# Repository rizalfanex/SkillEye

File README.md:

# SkillEye: Skeleton-Based Motion Quality Analysis for Racket Sports

Submission for the 8th CTCI Science and Technology Creativity Competition 2026 (Sports theme).

## Abstract

Existing racket-sport analytics apps (e.g. SwingVision) center on ball tracking and match
outcome — where the ball landed, who won the point. SkillEye instead analyzes the player's
*movement*, extracting a normalized 2D skeleton from swing video with RTMPose and modeling it
with a Spatio-Temporal Graph Convolutional Network (ST-GCN), toward the goal of a per-swing
motion-quality score with joint/phase-level error detection and rule-based correction feedback.
This addresses both the "training methods" and "injury prevention" sub-themes of the
competition through one shared representation.

This document reports the technical work completed to date on the [THETIS](https://github.com/THETIS-dataset/dataset)
tennis dataset: a validated pose-extraction pipeline (1,980/1,980 clips, 0 failures), a 6-class
stroke-type classifier (**81.7% ± 4.9%**, 5-fold subject-disjoint cross-validation), and a
beginner-vs-expert motion-quality proxy classifier (**82.4% ± 3.8%**). Both are real trained
results on held-out subjects, not projected targets. A rule-based v1 of that quality-score
system — phase detection, per-joint deviation from expert-clip templates, and generated
correction suggestions — is implemented and demonstrated through an accompanying Streamlit UI.
Section 4 discusses what these results do and do not establish, and Section 5 lays out the
remaining work toward the full quality-score system.

## 1. Introduction

### 1.1 Motivation

Amateur and intermediate racket-sport players typically improve technique through in-person
coaching, which is expensive, geographically limited, and infrequent relative to how often
players practice alone. Video-based swing analysis could close this gap, but existing consumer
tools (SwingVision and similar) are built around ball-tracking and scorekeeping — they answer
"did the shot land in" rather than "what did the player's body do." Movement quality is the
input a coach actually reasons about (elbow position at contact, hip rotation timing, follow-through),
and it is not derivable from ball trajectory alone.

### 1.2 Related Work

The technical approach follows two established lines of work rather than proposing new
architectures: **RTMPose** for real-time 2D human pose estimation, and **ST-GCN**
(Yan, Xiong & Lin, 2018) for skeleton-based action recognition, which models a keypoint sequence
as a spatio-temporal graph — spatial edges follow the human skeleton, temporal edges connect the
same joint across frames. The novelty in SkillEye is the application: using this representation
not just to classify *what* stroke was performed (a mature task), but as the foundation for
scoring *how well* it was performed, which is comparatively unexplored for racket sports at
consumer scale. The THETIS dataset itself (Gourgari et al., CVPR 2013 workshop) was built for
action recognition, not quality assessment — Section 2.1 and 4.1 discuss what that means for
how it can and cannot be used here.

A useful point of comparison is Wagner's tennis serve dataset (2024, [jasnwag/tennis_serve_dataset](https://github.com/jasnwag/tennis_serve_dataset)),
which takes a near-opposite set of trade-offs to THETIS: broadcast footage of the 2024 US Open,
109 professional players, 5,966 serves, with **3D** pose (RTMPose → MotionBERT lifting →
DTW-aligned) rather than 2D, and — notably — an actual serve-quality classification task
(84.0% reported), where THETIS offers only the subject-level beginner/expert proxy used in
Section 2.4/3.2. Table 2 summarizes the contrast:

**Table 2.** Dataset comparison.

| | THETIS (this work) | Wagner tennis serve dataset |
|---|---|---|
| Source | controlled gym recording (Kinect) | broadcast video, 2024 US Open |
| Camera angle | near-frontal | broadcast (side/elevated) |
| Pose dimensionality | 2D (COCO-17) | 3D (COCO-17, MotionBERT-lifted) |
| Subjects | 55 (31 beginner, 24 expert) | 109 professional players |
| Stroke coverage | 12 categories, all strokes | serves only |
| Clips | 1,980 | 5,966 serves |
| Quality ground truth | none (subject-level skill label only) | serve-quality labels available |
| License | dataset's own terms | CC BY 4.0 |

The two datasets are complementary rather than substitutable for this project: THETIS's frontal
angle and 2D pose match what a consumer phone camera can realistically capture (the deployment
target), while the serve dataset's 3D pose and side/elevated broadcast angle are closer to what
the biomechanical joint-angle rules in Section 4.7 of the proposal actually need, and its
existing quality labels are exactly the kind of ground truth Path A/B (Section 5) is trying to
establish independently. It is treated here as a comparative reference and a candidate source
for cross-dataset validation once the 2D pipeline has a 3D-compatible variant, not (yet) as
training or evaluation data for the models in Section 3 — see Section 5 for that as a concrete
next step.

### 1.3 Contributions

1. A validated, resumable pose-extraction pipeline from raw racket-sport video to normalized,
   tracked, single-subject skeleton sequences (Section 2.2).
2. A stroke-type classifier trained from scratch on the extracted skeletons, evaluated with
   5-fold subject-disjoint cross-validation rather than a single split (Section 3.1).
3. Evidence, from a dedicated experiment, that motion *quality* (not just stroke type) is
   learnable from this same skeleton representation — using THETIS's beginner/expert metadata
   as a weak proxy label ahead of real coach-rating ground truth (Section 3.2).
4. An honest accounting of what this dataset cannot yet support (Section 4.1) and a concrete
   plan for closing that gap (Section 5).

## 2. Methodology

### 2.1 Dataset

[THETIS](https://github.com/THETIS-dataset/dataset) (Gourgari et al., 2013) provides 1,980 RGB
video clips across 12 tennis action categories, performed by 55 subjects (**p1–p31 labeled
beginner, p32–p55 labeled expert** per the dataset's own metadata), recorded at ~17–19 fps,
640×480, with a Kinect camera facing the subject (near-frontal, not side-on). Only the
`VIDEO_RGB` subset is used — `VIDEO_Skelet2D/3D` uses Kinect's joint definition (not COCO-17,
the format the deployed pipeline actually produces) and covers only 1,217 of 8,374 sequences,
so it would not be representative even if remapped.

Class composition after the merge described in 2.3 (Table 1):

| stroke | THETIS sub-categories merged | clips |
|---|---|---:|
| backhand | backhand, backhand2hands, backhand_slice | 495 |
| forehand | forehand_flat, forehand_openstands, forehand_slice | 495 |
| backhand_volley | backhand_volley | 165 |
| forehand_volley | forehand_volley | 165 |
| serve | flat_service, kick_service, slice_service | 495 |
| smash | smash | 165 |
| **total** | | **1,980** |

By skill label: 1,116 clips from 31 beginner subjects, 864 clips from 24 expert subjects.

**Measured limitations relevant to this project** (checked directly on sample frames, not
assumed from the dataset paper): the ~17-19fps frame rate is below what the proposal's
biomechanical rules assume is needed to resolve fast strokes (e.g. serves), and the
near-frontal camera angle does not capture the side-on view that joint-angle-based
error-detection rules require. THETIS is therefore treated here as suitable for pretraining the
motion representation and for stroke/skill classification (both established, well-precedented
tasks — this is what Sections 2.3–2.4 and 3 use it for), but **not** as a substitute for
purpose-collected side-view footage when the actual per-swing quality-score model is built
(Section 5).

### 2.2 Pose Extraction Pipeline

Each clip is processed frame-by-frame with **RTMPose** (`rtmpose-s_simcc-body7`, lightweight
mode, COCO-17 keypoints) for pose estimation and **YOLOX-tiny** for person detection, both run
via `rtmlib`/ONNX Runtime. Frames may contain more than one person (other players/staff visible
in the gym), so a dedicated tracking step selects a single, temporally consistent subject:

1. **Primary-subject selection** — on the first frame, the person with the largest visible
   bounding box (among detections with ≥3 confidently-visible joints) is chosen as the subject.
   On subsequent frames, the detection with the nearest hip-center to the previous frame's
   selection is kept, which prevents identity swaps between the subject and any other person
   entering the frame (largest-bbox alone is insufficient once multiple people are present).
2. **Confidence-based interpolation** — per joint, frames below a 0.3 confidence threshold are
   linearly interpolated from the nearest confident frames on either side (no extrapolation at
   clip boundaries). Clips where the primary subject is confidently visible in under 50% of
   frames are dropped rather than interpolated across too large a gap.
3. **Normalization** — each frame is re-centered on the hip midpoint and scaled by
   shoulder-to-hip (torso) length, so the model learns the *shape* of the motion rather than the
   subject's distance from or position relative to the camera.

Result: **1,980/1,980 clips extracted successfully, 0 dropped, 0 failed**, ~1.4s/clip. Code:
`ml/skilleye/skeleton_pipeline.py` (steps above), `ml/skilleye/batch_extract.py` (CLI batch runner,
resumable — skips clips that already have output on disk, so an interrupted run can restart
without redoing completed work).

### 2.3 Stroke Classification Model

THETIS's 12 action categories are merged into 6 target classes (Table 1) reflecting the strokes
the proposal is actually built around — `serve` merges the three service sub-types (genuinely
one stroke with different spin), but `forehand_volley` and `backhand_volley` are kept **separate**
rather than merged into a single "volley" class, since they are visually and kinematically
distinct motions (an earlier iteration that merged them made that class disproportionately hard
to classify — see Section 4.1).

**Architecture**: a compact ST-GCN — 6 spatio-temporal blocks operating on the COCO-17 skeleton
graph (symmetric-normalized adjacency, self-loops included), channel widths 32→64→128→256,
global average pooling, linear classification head. Input is a 4-channel tensor per joint per
frame: 2D position plus its temporal finite-difference (velocity), giving the model direct
access to motion speed/direction rather than only inferring it across pooled layers. Each clip
is time-resampled to a fixed 64 frames (linear interpolation) so variable clip lengths (THETIS
clips range from roughly 2 to 8+ seconds) can be batched. Code: `ml/skilleye/stgcn_model.py`.

**Training**: Adam (lr 1e-3, weight decay 1e-4), cosine-annealed learning rate, class-weighted
cross-entropy (classes are imbalanced — see Table 1), 80–100 epochs, batch size 32. With only 55
subjects total, label-preserving data augmentation is applied at train time: left-right mirroring
(negate the x-coordinate and swap left/right joint indices — a mirrored forehand is still a
forehand, just as a left-handed player's would look), random temporal cropping (retain a random
85–100%-length contiguous sub-window before resampling), and small Gaussian coordinate jitter
(σ=0.02, in normalized units). Code: `ml/skilleye/train_stroke_classifier.py`.

### 2.4 Beginner-vs-Expert Motion-Quality Proxy Model

To test whether motion *quality* — not just stroke identity — is learnable from this
representation, a second model is trained on THETIS's beginner/expert subject-level label
(Section 2.1) as a weak proxy for swing quality, ahead of collecting real coach ratings
(Section 5). Two approaches were tried, reported both for transparency:

- **v1 — hand-crafted features + logistic regression** (`ml/skilleye/beginner_expert_check.py`):
  9 interpretable per-clip features (mean/std swing speed, jerk, elbow/knee joint-angle
  variance, wrist extension range) fed into a linear classifier.
- **v2 — ST-GCN** (`ml/skilleye/train_beginner_expert_stgcn.py`): identical architecture and
  augmentation to Section 2.3, but with a binary beginner/expert output head, trained directly
  on the raw skeleton sequence rather than hand-summarized statistics.

### 2.5 Evaluation Protocol

All splits are **subject-disjoint**: no subject's clips appear in both the training and
validation sets. THETIS clips from the same subject are highly correlated (same body, same
camera, same session), so a clip-level random split would leak subject identity into validation
and overstate accuracy — the model would partly be recognizing *people*, not strokes or skill.

Headline numbers use **5-fold subject-disjoint cross-validation** (`ml/skilleye/cross_validate.py`):
subjects are split into 5 folds, stratified so each fold's held-out group keeps a
beginner/expert mix; each fold trains a fresh model on the other 4 folds' subjects (~44) and
evaluates on the held-out fold's subjects (~11). This is reported as **mean ± standard
deviation across folds**, rather than a single split's number, because with only 55 subjects a
single split's held-out accuracy depends materially on *which* subjects happened to be held
out — the fold-to-fold spread reported in Section 3 is itself informative about that variance.

### 2.6 Quality Scoring System

The proposal's central promised feature -- a per-swing motion-quality score with
per-joint/phase error detection and rule-based correction suggestions (Section 4.7) -- is
implemented here as a rule-based comparison against expert-clip statistics, not a learned
regression model. No coach-rating ground truth exists yet (Path A/B, Section 5), so a
supervised quality-score model cannot be trained honestly; this is an explicitly-scoped
interim v1, in the same spirit as the v1->v2->v3 iterations already described for the
classifiers above.

**Phase detection** (`ml/skilleye/quality/phases.py`): each clip's dominant wrist (whichever
moves more overall -- a proxy for the hitting arm, since THETIS doesn't label handedness)
is used to find the contact frame (peak wrist speed, a standard swing-analysis heuristic),
splitting the clip into three phases: backswing, a short window around contact, and
follow-through.

**Joint angles** (`ml/skilleye/quality/angles.py`): per phase, four flexion angles
(left/right elbow, left/right knee) plus a trunk-rotation proxy (shoulder-line vs.
hip-line angle) are averaged into one scalar per (phase, joint).

**Expert templates** (`ml/skilleye/build_expert_templates.py`, run once offline): for each
stroke class, the mean and standard deviation of each (phase, joint) scalar across that
class's expert-labeled clips, computed only from the training side of this project's
standard subject-disjoint split (Section 2.5) -- never from the held-out validation
subjects, which remain available as genuinely unseen demo inputs.

**Scoring** (`ml/skilleye/quality/score.py`): a query clip's (phase, joint) scalars are
z-scored against its predicted stroke's template; |z| > 1.5 is flagged and mapped to a
fixed coaching-tip sentence, and the overall 0-100 score is a monotonic function of mean
absolute deviation. `SCORE_SCALE`/`FLAG_THRESHOLD` are sanity-checked (Section 3.3), not
formally calibrated -- that calibration is exactly what Path A/B ground truth would
enable.

**Demo UI** (`ml/skilleye/app.py`, Streamlit): pick a stroke category and a sample clip
(restricted to the held-out validation subjects, so every demo score is computed against
a template that never saw that subject) and see the skeleton, the existing stroke
classifier's prediction, the quality score, the per-phase/joint table, and the correction
suggestions together. Run with `streamlit run app.py` from `ml/skilleye/`.

**AI-generated explanation (optional)**: a "Generate AI explanation" button in the demo
UI rewrites the already-flagged deviations above into one natural coaching paragraph via
an LLM (NVIDIA's build.nvidia.com API). The LLM is only ever given the (phase, joint,
z-score) rows the rule-based system already flagged — it never inspects raw angles or
introduces a new diagnosis — so this is a communication layer over the existing,
smoke-checked scoring system, not a new source of truth. It requires an `NVIDIA_API_KEY`
environment variable; without one (or if the API call fails for any reason), the button
falls back to a short warning and the rule-based suggestions list above remains the
result, so the demo never depends on network access to function. Design:
`docs/superpowers/specs/2026-07-23-llm-correction-explainer-design.md`.

### 2.7 Sensor-Fusion Extension (Prototype)

A team discussion identified a concrete limitation already described in Section 4.1: a
single frontal 2D camera cannot see racket-face angle or wrist-snap dynamics at contact —
exactly the kind of high-frequency, off-camera-plane signal a racket-mounted IMU
(accelerometer + gyroscope) would capture directly. This section covers both halves of
that work: the hardware (designed by a teammate, in parallel with everything else in this
document) and the software fusion prototype that will eventually consume its data.

**Hardware — rev1.0 schematics** (designed by [@kyriosaa](https://github.com/kyriosaa)):
an ESP32-C6-WROOM-1 microcontroller paired with an ST LSM6DSO 6-axis IMU
(accelerometer + gyroscope) for sensing, a TP4056/DW01A/FS8205A single-cell Li-ion
charging and protection circuit, and an HT7833 regulator for the board's 3.3V rail.
Full KiCad project: `hardware/skilleye_prototype/` (schematics, PCB layout, component
libraries, datasheets); rendered schematic sheets below, source at
`docs/schematics/prototype/rev1.0/`.

| Charging | MCU + IMU | Regulator |
|---|---|---|
|  |  |  |

This is schematic-complete design work, not yet a built board: no physical prototype has
been assembled, no firmware has been written, and no real sensor data has been collected.
The modeling work below is written accordingly — it does not depend on or wait for the
physical board, and does not claim to have used it.

**Software architecture** (`ml/skilleye/imu_fusion.py`): `STGCN` is refactored to expose
its pooled pre-classifier features via `extract_features()` (`ml/skilleye/stgcn_model.py`,
backward compatible — every existing caller is unaffected). A small `IMUEncoder` (1D-CNN
over a 6-channel accelerometer+gyroscope stream) is fused with that skeleton branch via
concatenation before one classification head (`FusedBeginnerExpertModel`), targeting the
beginner/expert distinction specifically, since that is the axis this sensor is meant to
inform.

**Synthetic data, stated plainly**: because no real sensor data exists yet,
`synthetic_imu_from_skeleton()` derives a placeholder signal from the skeleton itself
(wrist acceleration, forearm angular velocity) rather than from a real sensor. This signal
is, by construction, redundant with information the skeleton branch already has access to
— so `train_beginner_expert_fusion_prototype.py`'s output is a demonstration that the
fusion architecture and training loop work end to end, **not an accuracy result**, and its
numbers must not be cited alongside Section 3.2's cross-validated 82.4% ± 3.8%.

**Path to real data**: a documented collection protocol (~100-200 Hz logging, a tap-based
manual sync event between the video and IMU streams, resampled to the same fixed frame
count skeletons already use) is in
`docs/superpowers/specs/2026-07-23-imu-fusion-prototype-design.md` — written before the
rev1.0 schematic existed, so it describes a generic MPU6050+ESP32 pairing rather than the
LSM6DSO+ESP32-C6 above; the collection method (sampling rate, sync approach) still applies
unchanged. Swapping `synthetic_imu_from_skeleton()`'s call site for a real-data loader is
the only code change needed once the board above is built and recordings exist.

## 3. Results

### 3.1 Stroke Classification

**81.7% ± 4.9%** held-out accuracy (6-way; majority-class baseline 16.7%), fold range
72.5%–86.1%.

| class | precision | recall | f1 | support |
|---|---:|---:|---:|---:|
| backhand | 0.79 | 0.90 | 0.84 | 495 |
| forehand | 0.87 | 0.79 | 0.83 | 495 |
| backhand_volley | 0.66 | 0.63 | 0.64 | 165 |
| forehand_volley | 0.68 | 0.67 | 0.68 | 165 |
| serve | 0.93 | 0.88 | 0.90 | 495 |
| smash | 0.73 | 0.78 | 0.75 | 165 |

`serve` is the strongest class — mechanically the most distinct motion (toss + overhead
strike). The volley classes are weakest, and the confusion matrix shows *why*: forehand_volley
is confused primarily with forehand, backhand_volley primarily with backhand — i.e. a volley
shares arm-swing kinematics with its groundstroke counterpart, and the near-frontal 2D camera
does not capture the footwork/court-position difference (volleys are played closer to the net)
that would otherwise disambiguate them. This is discussed further in Section 4.1.

### 3.2 Beginner vs. Expert

**82.4% ± 3.8%** held-out accuracy (2-way; majority-class baseline 54.6%), fold range
78.5%–89.7%. The v1→v2 progression:

| iteration | method | held-out accuracy |
|---|---|---|
| v1 | 9 hand-crafted features + logistic regression, single split | 58.6% (baseline 54.6%) |
| v2 | ST-GCN on raw skeleton sequence, single split | 76.0% |
| **v3** | **ST-GCN, 5-fold cross-validation** | **82.4% ± 3.8%** |

v1 established that *population-level* differences between beginner and expert clips are real
and highly significant (Welch's t-test on all 9 features, p<0.02, most p<1e-10, n=1,980) —
notably, **experts showed higher swing speed, jerk, and joint-angle variance than beginners, not
lower**, i.e. expert swings read as more dynamic/forceful rather than smoother in this dataset,
which should inform how a smoothness-based quality heuristic is weighted. But v1's linear model
on those 9 summary statistics only reached 58.6% held-out accuracy — barely above baseline,
meaning the signal existed in aggregate but wasn't usable per-subject with simple features.

v2 replaced the hand-crafted features with the same ST-GCN architecture used for stroke
classification, trained directly on the raw skeleton sequence, and reached 76.0% on a single
split. v3 cross-validated that result and found it was, if anything, an *unfavorable* split —
the cross-validated mean (82.4%) is higher than the single-split number, with folds ranging
78.5%–89.7% (Table above; per-class breakdown: beginner precision 0.85/recall 0.83, expert
precision 0.79/recall 0.82, summed over all 5 folds' held-out predictions).

### 3.3 Quality Scoring Smoke Check

No formal ground truth exists yet to validate quality scores against (Section 2.6) --
this instead checks the one directional claim the system must satisfy to be credible:
held-out expert clips should score higher on average than held-out beginner clips, per
stroke class, against that stroke's own expert template.

| stroke | expert mean | beginner mean | experts higher? |
|---|---:|---:|---|
| backhand | 89.8 | 86.2 | yes |
| backhand_volley | 90.9 | 84.6 | yes |
| forehand | 90.1 | 86.6 | yes |
| forehand_volley | 88.9 | 77.5 | yes |
| serve | 87.6 | 87.0 | yes |
| smash | 87.9 | 87.1 | yes |

Experts scored higher on every stroke with held-out data (`ml/skilleye/smoke_check_quality_scoring.py`).
This is a sanity check, not a validation -- it confirms the scoring system's direction
is sane on the same subject-level proxy label used in Section 3.2, not that its absolute
scores or flagged joints are correct at the level of a real coach's judgment. That
remains gated on Path A/B ground truth (Section 5).

The aggregate numbers above are a directional average -- the actual per-clip output looks
like this (two real held-out `forehand_volley` clips, the largest expert/beginner gap in
the table above):

The beginner clip's flagged joints are concrete and actionable (left elbow over-extended,
right elbow under-extended, left knee not bent enough at contact) rather than an opaque
number -- this is what "rule-based correction suggestions" (proposal Section 4.7) actually
produces today, not a mockup of what it might eventually say.

## 4. Discussion

### 4.1 Limitations

- **Camera geometry limits stroke disambiguation.** The volley/groundstroke confusion in
  Section 3.1 is a direct consequence of THETIS's near-frontal camera — footwork and
  court-position cues that would resolve it are not visible from that angle. Side-view footage
  (planned, Section 5) should address this directly, not just improve accuracy but make the
  representation richer for the eventual per-phase error detection this project needs.
- **The beginner/expert label is a subject-level proxy, not a per-swing quality score.** THETIS
  labels an entire subject as beginner or expert; it says nothing about whether a specific swing
  within that subject's clips was a particularly good or bad execution. The precision/recall
  asymmetry noted in Section 3.2 (the model calls some beginner clips "expert" and vice versa)
  is consistent with this — a beginner's better attempts plausibly look expert-ish in isolation,
  and the reverse. Section 3.2's result demonstrates that quality-relevant signal exists and is
  learnable, which de-risks the project's core premise; it does not by itself produce the
  continuous, per-swing quality score the finished system needs.
- **Frame rate.** ~17–19fps may under-resolve the fastest phases of a serve or smash relative to
  the 60fps the original proposal assumed necessary; this has not yet been quantified directly
  (e.g. by comparing model behavior on down-sampled higher-fps footage) and is flagged as an
  open question rather than a settled limitation.
- **Sample size for cross-validation.** 55 subjects is enough to show fold-to-fold variance
  (Section 3, 4.9 and 3.8 percentage-point standard deviations) but not enough to make that
  variance estimate itself highly precise — it indicates real single-split fragility rather than
  pinning down an exact confidence interval.

### 4.2 Implications for the Quality-Score System

Taken together, Sections 3.1 and 3.2 support two concrete design decisions for the system
described in the proposal's Section 4.7: (1) stroke-type classification is solved to a
practical standard on this representation and can run as a preprocessing step before
stroke-specific quality rules are applied, and (2) motion quality is measurable from the same
representation in principle, but the production quality-score model will need either
per-swing ground truth (real coach ratings, or synthetic perturbation of known-good motion —
both already planned as Path A/B) or a training signal richer than a subject-level label,
because Section 3.2's result is a proof of learnability, not a finished quality metric.
Section 2.6/3.3's rule-based scorer is a further step in that direction -- a working,
demonstrable system rather than only a proof of concept -- but it is calibrated by a
sanity check, not by the coach ratings or synthetic ground truth that would let its
scores be trusted at face value.

## 5. Conclusion and Future Work

This work establishes, with real trained and cross-validated results rather than projected
targets, that (1) a resumable, validated pipeline exists from raw racket-sport video to a
normalized skeleton representation, (2) stroke type is classifiable from that representation to
a practical standard (81.7% ± 4.9%, 6-way), and (3) motion quality signal — not just stroke
identity — is present and learnable in the same representation (82.4% ± 3.8% on a weak proxy
label), which supports the project's central premise ahead of collecting stronger ground truth.

Remaining work, in priority order:

1. **Team/university/advisor/contact fields** in the competition proposal — still placeholders;
   blocks submission eligibility independent of all technical progress above.
2. **Path B: coach-rated ground truth** — recruit coaches to blind-rate real swings, to be
   correlated against model output (target r > 0.7). Longest lead time item; should run in
   parallel with, not after, further technical work.
3. **Own side-view, higher-frame-rate recordings, plus a physical sensor board** —
   required for the joint-angle-based error-detection rules in Section 4.7, expected to
   resolve the volley/groundstroke confusion identified in Section 4.1, and needed to move
   Section 2.7's sensor-fusion prototype from synthetic to real data. Rev1.0 schematics
   (ESP32-C6 + LSM6DSO) exist in `hardware/skilleye_prototype/`; assembly, firmware, and
   the collection protocol (sampling rate, synchronization method) are scoped in
   `docs/superpowers/specs/2026-07-23-imu-fusion-prototype-design.md`. Once real logs
   exist, retraining and cross-validating `FusedBeginnerExpertModel` on them — following
   the same 5-fold rigor as Section 3.2 — is the follow-up this prototype sets up for.
4. **Path A: synthetic perturbation** of known-good motion (known joint-angle/timing offsets
   injected into skilled-athlete clips) as a complementary, coach-independent ground-truth
   source for the quality-score model.
5. **A learned quality-score model** (proposal Section 4.7) — Section 2.6/3.3 delivers a
   working rule-based v1 (phase detection, joint angles, expert-template comparison); once
   ground truth from (2) and/or (4) is available, that data enables replacing or
   augmenting the rule-based scorer with a trained regression model, and calibrating
   `FLAG_THRESHOLD`/`SCORE_SCALE` against real quality judgments instead of a directional
   sanity check.
6. **Cross-dataset validation against the Wagner tennis serve dataset** (Section 1.2) — its
   existing serve-quality labels are an external, independently-collected signal that could
   validate whether the quality-relevant patterns found in Section 3.2 generalize beyond THETIS
   and beyond amateur players. This requires extending the 2D pipeline to accept its 3D pose
   format (or projecting its 3D keypoints to 2D for direct compatibility) — not yet attempted,
   flagged here as a concrete, scoped next step rather than folded into the results above.

## 6. Reproducibility

```
ml/skilleye/                       pipeline and modeling code
  skeleton_pipeline.py             RTMPose output -> tracked subject -> normalized skeleton (§2.2)
  batch_extract.py                 CLI batch runner over a THETIS-shaped folder tree (resumable)
  stroke_dataset.py                category merging (Table 1), subject-disjoint/k-fold splitting
  stgcn_model.py                   ST-GCN architecture, COCO-17 skeleton graph (§2.3)
  train_stroke_classifier.py       stroke classifier, single split
  train_beginner_expert_stgcn.py   beginner/expert ST-GCN, single split (§2.4)
  beginner_expert_check.py         beginner/expert hand-crafted-feature baseline, v1 (§2.4)
  cross_validate.py                5-fold cross-validation for both classifiers (§2.5)
  generate_figures.py              renders ml/results/figures/*.png from the metrics JSONs
  quality/                         phase detection, joint angles, template scoring (§2.6)
  build_expert_templates.py        builds ml/results/quality_templates/templates.json (§2.6)
  smoke_check_quality_scoring.py   experts-score-higher-than-beginners sanity check (§3.3)
  generate_qualitative_figures.py  renders the stroke-gallery and quality-comparison examples (§2.6/3.3)
  app.py                           Streamlit demo UI (§2.6) -- run: streamlit run app.py
  quality/llm_explainer.py         optional LLM-generated correction paragraphs (§2.6, needs NVIDIA_API_KEY)
  imu_fusion.py                    synthetic IMU signal + fusion model prototype (§2.7)
  train_beginner_expert_fusion_prototype.py   trains the fusion prototype (synthetic data, §2.7)
  requirements.txt
  README.md                        environment setup notes (incl. GPU-specific gotchas)

ml/results/
  RESULTS_SUMMARY.md                supplementary detail beyond what's inlined above
  figures/                          PNGs embedded above; regenerate with generate_figures.py / generate_qualitative_figures.py
  quality_templates/                templates.json: per-stroke expert (phase, joint) statistics (§2.6)
  imu_fusion_prototype/             prototype-only metrics (synthetic IMU data, §2.7) -- not a benchmark
  cross_validation/                 §3 headline numbers: per-fold + aggregated metrics
  beginner_expert_check.json        v1 (§2.4): hand-crafted features + logistic regression
  beginner_expert_stgcn/            v2 (§2.4): ST-GCN, single split, trained weights + metrics
  stroke_classifier/                early 5-class iteration, kept for reference
  stroke_classifier_v2/             6-class + augmentation, single split, trained weights + metrics

hardware/skilleye_prototype/       KiCad rev1.0 PCB project (§2.7): ESP32-C6 + LSM6DSO IMU,
                                    battery charging/regulation -- schematic only, not yet built
docs/schematics/prototype/rev1.0/  rendered schematic PDFs/SVGs for the board above
```

Dataset (not included in this repository — see `ml/skilleye/README.md` for how to fetch it):
[THETIS](https://github.com/THETIS-dataset/dataset), `VIDEO_RGB` + `papers` subsets only.

## References

- Gourgari, S., Goudelis, G., Karpouzis, K., & Kollias, S. (2013). THETIS: Three Dimensional
  Tennis Shots a Human Action Dataset. *CVPR Workshops*.
- Yan, S., Xiong, Y., & Lin, D. (2018). Spatial Temporal Graph Convolutional Networks for
  Skeleton-Based Action Recognition. *AAAI*.
- Jiang, T., et al. (2023). RTMPose: Real-Time Multi-Person Pose Estimation based on MMPose.
  *arXiv:2303.07399*.
- Wagner, J. (2024). Tennis Serve Analysis Dataset: 3D Pose Sequences from 2024 US Open Broadcast
  Video. https://github.com/jasnwag/tennis_serve_dataset (CC BY 4.0).

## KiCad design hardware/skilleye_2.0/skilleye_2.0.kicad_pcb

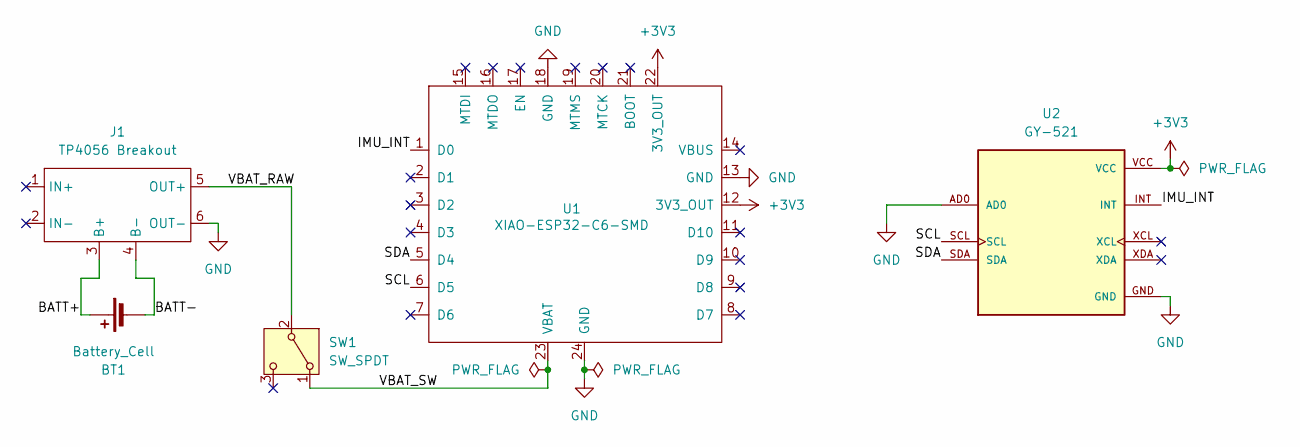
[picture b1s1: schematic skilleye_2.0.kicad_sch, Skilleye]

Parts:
BT1: Battery_Cell; SolderWirePad_2x01_SMD_1.5x3mm
J1: TP4056 Breakout; TP4056_breakout
SW1: SW_SPDT; SW_Slide_SPDT_Straight_CK_OS102011MS2Q
U1: XIAO-ESP32-C6-SMD
U2: GY-521; MODULE_GY-521; PARTREV NA

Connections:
+3V3: U1.12 (3V3_OUT), U1.22 (3V3_OUT), U2.VCC
/BATT+: BT1.1 (+), J1.3 (B+)
/BATT-: BT1.2 (-), J1.4 (B-)
/IMU_INT: U1.1 (D0), U2.INT
/SCL: U1.6 (D5), U2.SCL
/SDA: U1.5 (D4), U2.SDA
/VBAT_RAW: J1.5 (OUT+), SW1.2 (B)
/VBAT_SW: SW1.1 (A), U1.23 (VBAT)
GND: J1.6 (OUT-), U1.13 (GND), U1.18 (GND), U1.24 (GND), U2.AD0, U2.GND

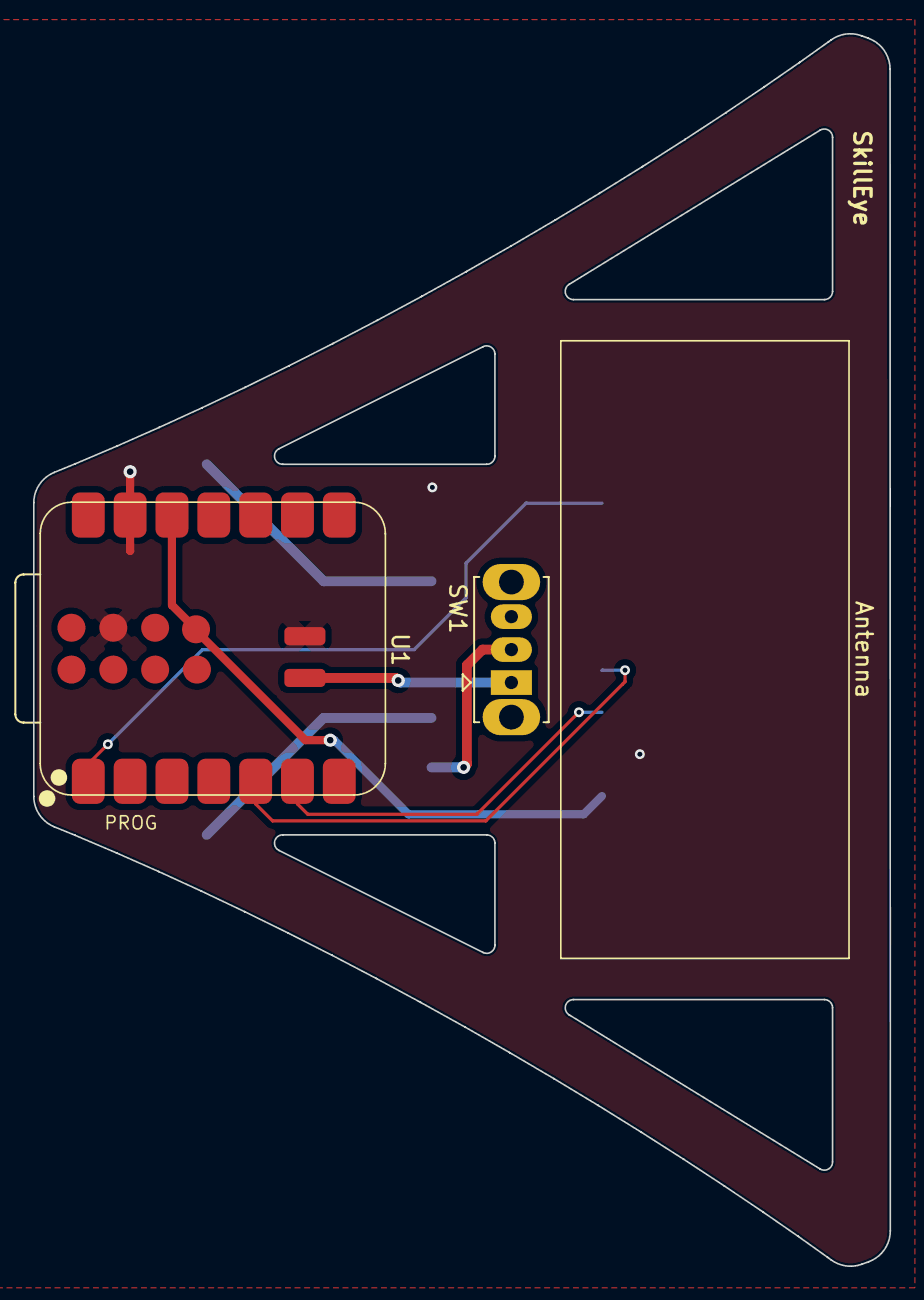
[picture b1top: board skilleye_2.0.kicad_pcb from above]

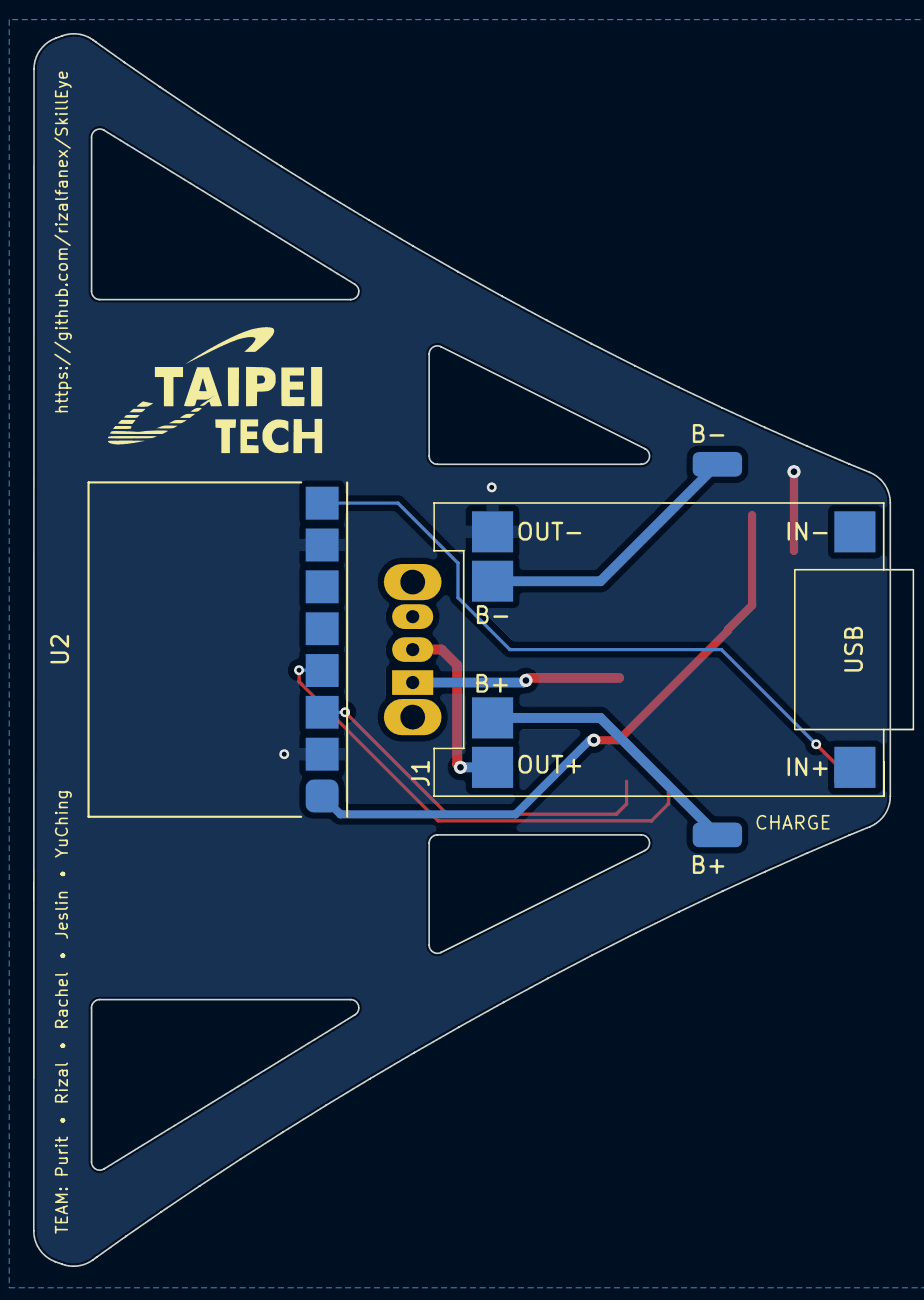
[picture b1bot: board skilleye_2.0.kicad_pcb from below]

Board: 2 copper layers, 52.0 x 74.8 mm, 5 parts (3 on the bottom side), 9 nets.

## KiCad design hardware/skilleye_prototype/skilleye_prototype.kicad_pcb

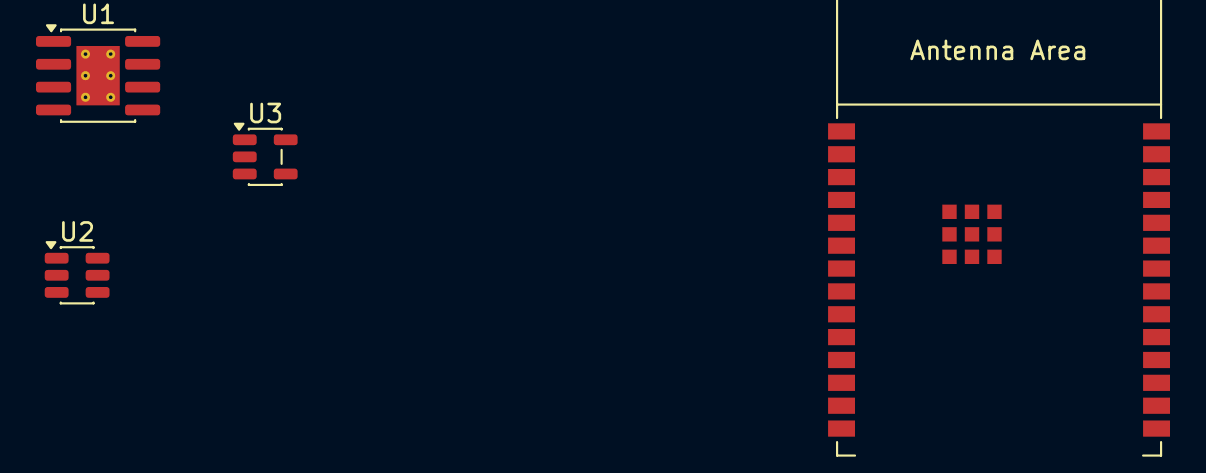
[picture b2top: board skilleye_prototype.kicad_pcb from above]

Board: 2 copper layers, 4 parts (0 on the bottom side), 4 nets, no tracks yet.

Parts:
U1: TP4056-42-ESOP8; SOIC-8-1EP_3.9x4.9mm_P1.27mm_EP2.41x3.3mm_ThermalVias
U2: DW01A; SOT-23-6
U3: HT7833; SOT-23-5
U4: ESP32-C6-WROOM-1 (N8); ESP32-C6-WROOM-1

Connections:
+5V: U1.4 (V_{CC}), U1.8 (CE)
BAT+: U1.5 (BAT), U3.1 (VIN), U3.3 (EN)
GND: U1.3 (GND), U1.9 (EPAD), U3.2 (GND)
unnamed: U4.1 (GND), U4.28 (GND), U4.29 (GND)
